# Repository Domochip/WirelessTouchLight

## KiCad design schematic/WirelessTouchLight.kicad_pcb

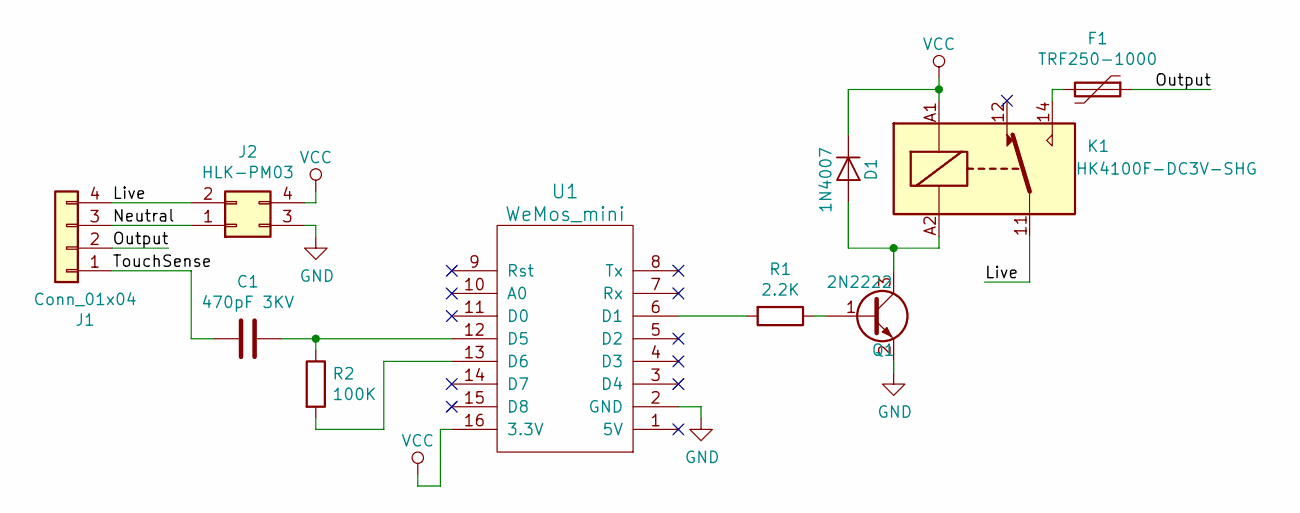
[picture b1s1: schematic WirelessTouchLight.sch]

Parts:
C1: 470pF 3KV; CP_Radial_Tantal_D4.5mm_P5.00mm
D1: 1N4007; D_SMA_Handsoldering
F1: TRF250-1000
J1: Conn_01x04; KF235-4P
J2: HLK-PM03; HLK-PM01
K1: HK4100F-DC3V-SHG; HK4100F
Q1: 2N2222; SOT-23_Handsoldering
R1: 2.2K; R_0805_HandSoldering
R2: 100K; R_0805_HandSoldering
U1: WeMos_mini; wemos-d1-mini-DIL-only

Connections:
/Live: J1.4, J2.2, K1.11
/Neutral: J1.3, J2.1
/Output: F1.1, J1.2
/TouchSense: C1.2, J1.1
GND: J2.3, Q1.2 (E), U1.2 (GND)
unnamed: C1.1, R2.1, U1.12 (D5)
unnamed: D1.2 (A), K1.A2, Q1.3 (C)
unnamed: F1.2, K1.14
unnamed: Q1.1 (B), R1.1
unnamed: R1.2, U1.6 (D1)
unnamed: R2.2, U1.13 (D6)
VCC: D1.1 (K), J2.4, K1.A1, U1.16 (3.3V)

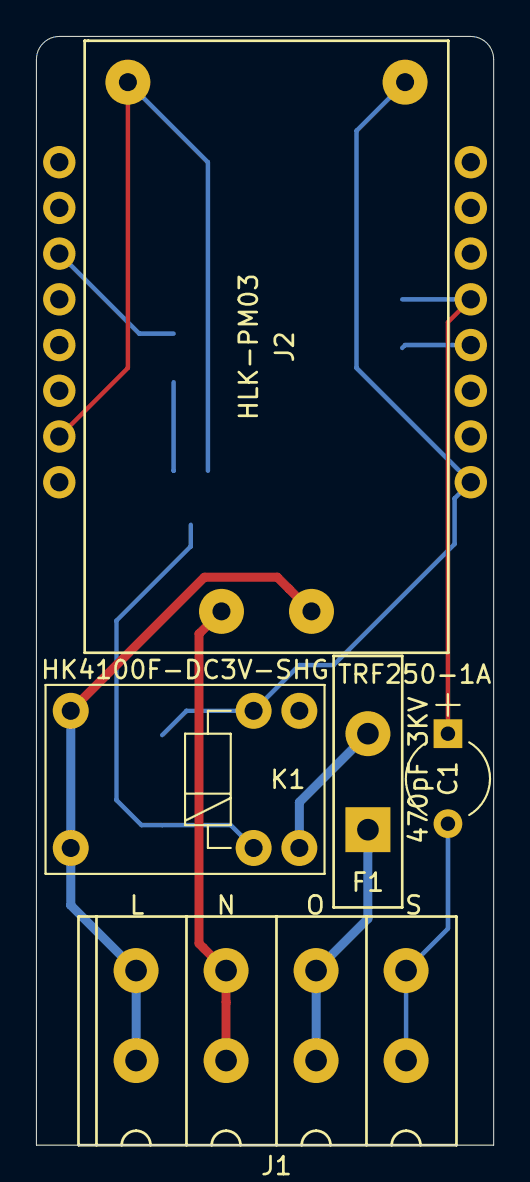
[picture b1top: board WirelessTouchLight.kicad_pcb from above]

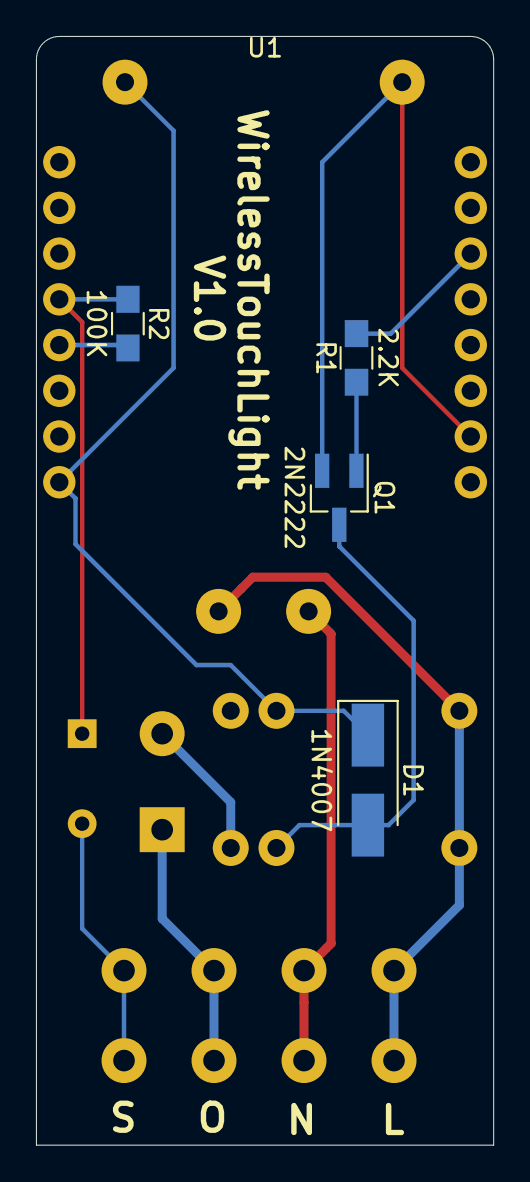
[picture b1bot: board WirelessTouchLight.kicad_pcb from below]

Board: 2 copper layers, 25.4 x 61.6 mm, 10 parts (5 on the bottom side), 12 nets.

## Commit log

2019-09-29 Add schematic
2019-10-01 remove bad main
2019-10-02 change to D1 Mini Shelly 1 is noisy!
2019-10-10 Update schematic
2019-10-13 Compatibility with Python3
2019-11-03 V0.9 Switch to D1 Mini
2019-11-03 up to Base V1.2.7
2019-11-03 V1.0
2019-11-03 Add Box
2019-11-03 Add Touch latency when order come from MQTT
2019-11-03 V1.1 Add different sampling while On or Off
2019-11-03 change hardcoded Serial usage
2019-11-07 Up to Base V1.2.8
2019-11-16 Up to Base V1.3.0
2019-11-17 Up to Base V1.3.1
2019-11-17 Base fix
2019-11-18 Up to Base V1.3.2
2019-11-22 Up to base V1.3.3
2019-11-23 Naming Convention
2019-11-24 Change to 470K Resistor
2019-11-24 Add Log
2019-11-24 Make Threshold a Variable
2019-11-24 V1.1.1 add last Capactive sensor Value to status
2019-11-26 Log AP Name
2019-12-02 fix Base
2019-12-02 Improve Sensing
2019-12-02 Add EventSource
2019-12-02 fix status1.html
2019-12-02 no RESCUE_BUTTON_WAIT
2019-12-02 Notify Web clients
2019-12-03 clean
2019-12-03 count 5 positive RAW detection
2019-12-03 Add PublishTicker
2019-12-03 json name correction
2019-12-03 Add threshold to Web config
2019-12-03 Remove CapacitiveSensor
2019-12-03 log + 2 measurement
2019-12-04 Use SEND_PIN to drive
2019-12-05 Improve status1.html
2019-12-05 Change Back to 100K resistor (470 too much noises)
2019-12-05 V1.2.0 switch back to CapacitiveSensor
2019-12-05 V1.2.1 Improve Web UI
2019-12-05 Don't use previousResult and positiveCount log
2019-12-05 Improve Web for calibration
2019-12-05 V1.2.3 use threshold level instead of sampleNumber
2020-03-07 Update schematic/PCB
2020-11-01 Up to base V1.4.0 /!\ Configuration lost after flash /!\
